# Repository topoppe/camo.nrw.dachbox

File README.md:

Im Rahmen des EFRE-geförderten Projektes CAMO.NRW forschen Mitarbeiter der Hochschule Ruhr West zusammen mit Kollegen der Bergischen Universität Wuppertal und der Bergischen Struktur- & Wirtschaftsförderungsgesellschaft an der Zukunft der automatisierten Mobilität. An der Hochschule bestand schon eine Experimentalplattform bestehend aus verschiedenen Kameras, Radarsensoren, LiDAR und mehreren GNSS.
Jene Plattform war im Kofferraum eines PKWs verbaut, jedoch ohne die Beachtung gängiger Sicherheitsvorschriften und Normen. 
Durch die komplexe Einbauweise war die gesamte Plattform an einen einzelnen PKW gebunden. 
Im Rahmen dieser Arbeit wurde die vorhandene Sensortechnik auf einem austauschbaren Geräteträger montiert. Hierbei wurde sowohl auf Sicherheitsvorschriften als auch auf die einfache Montagemöglichkeit auf verschiedenen PKW geachtet. 
Der entstandene Geräteträger kann nun sowohl mobil als auch stationär, auf einem beliebigen PKW montiert oder in einer Laborumgebung ohne PKW genutzt werden.

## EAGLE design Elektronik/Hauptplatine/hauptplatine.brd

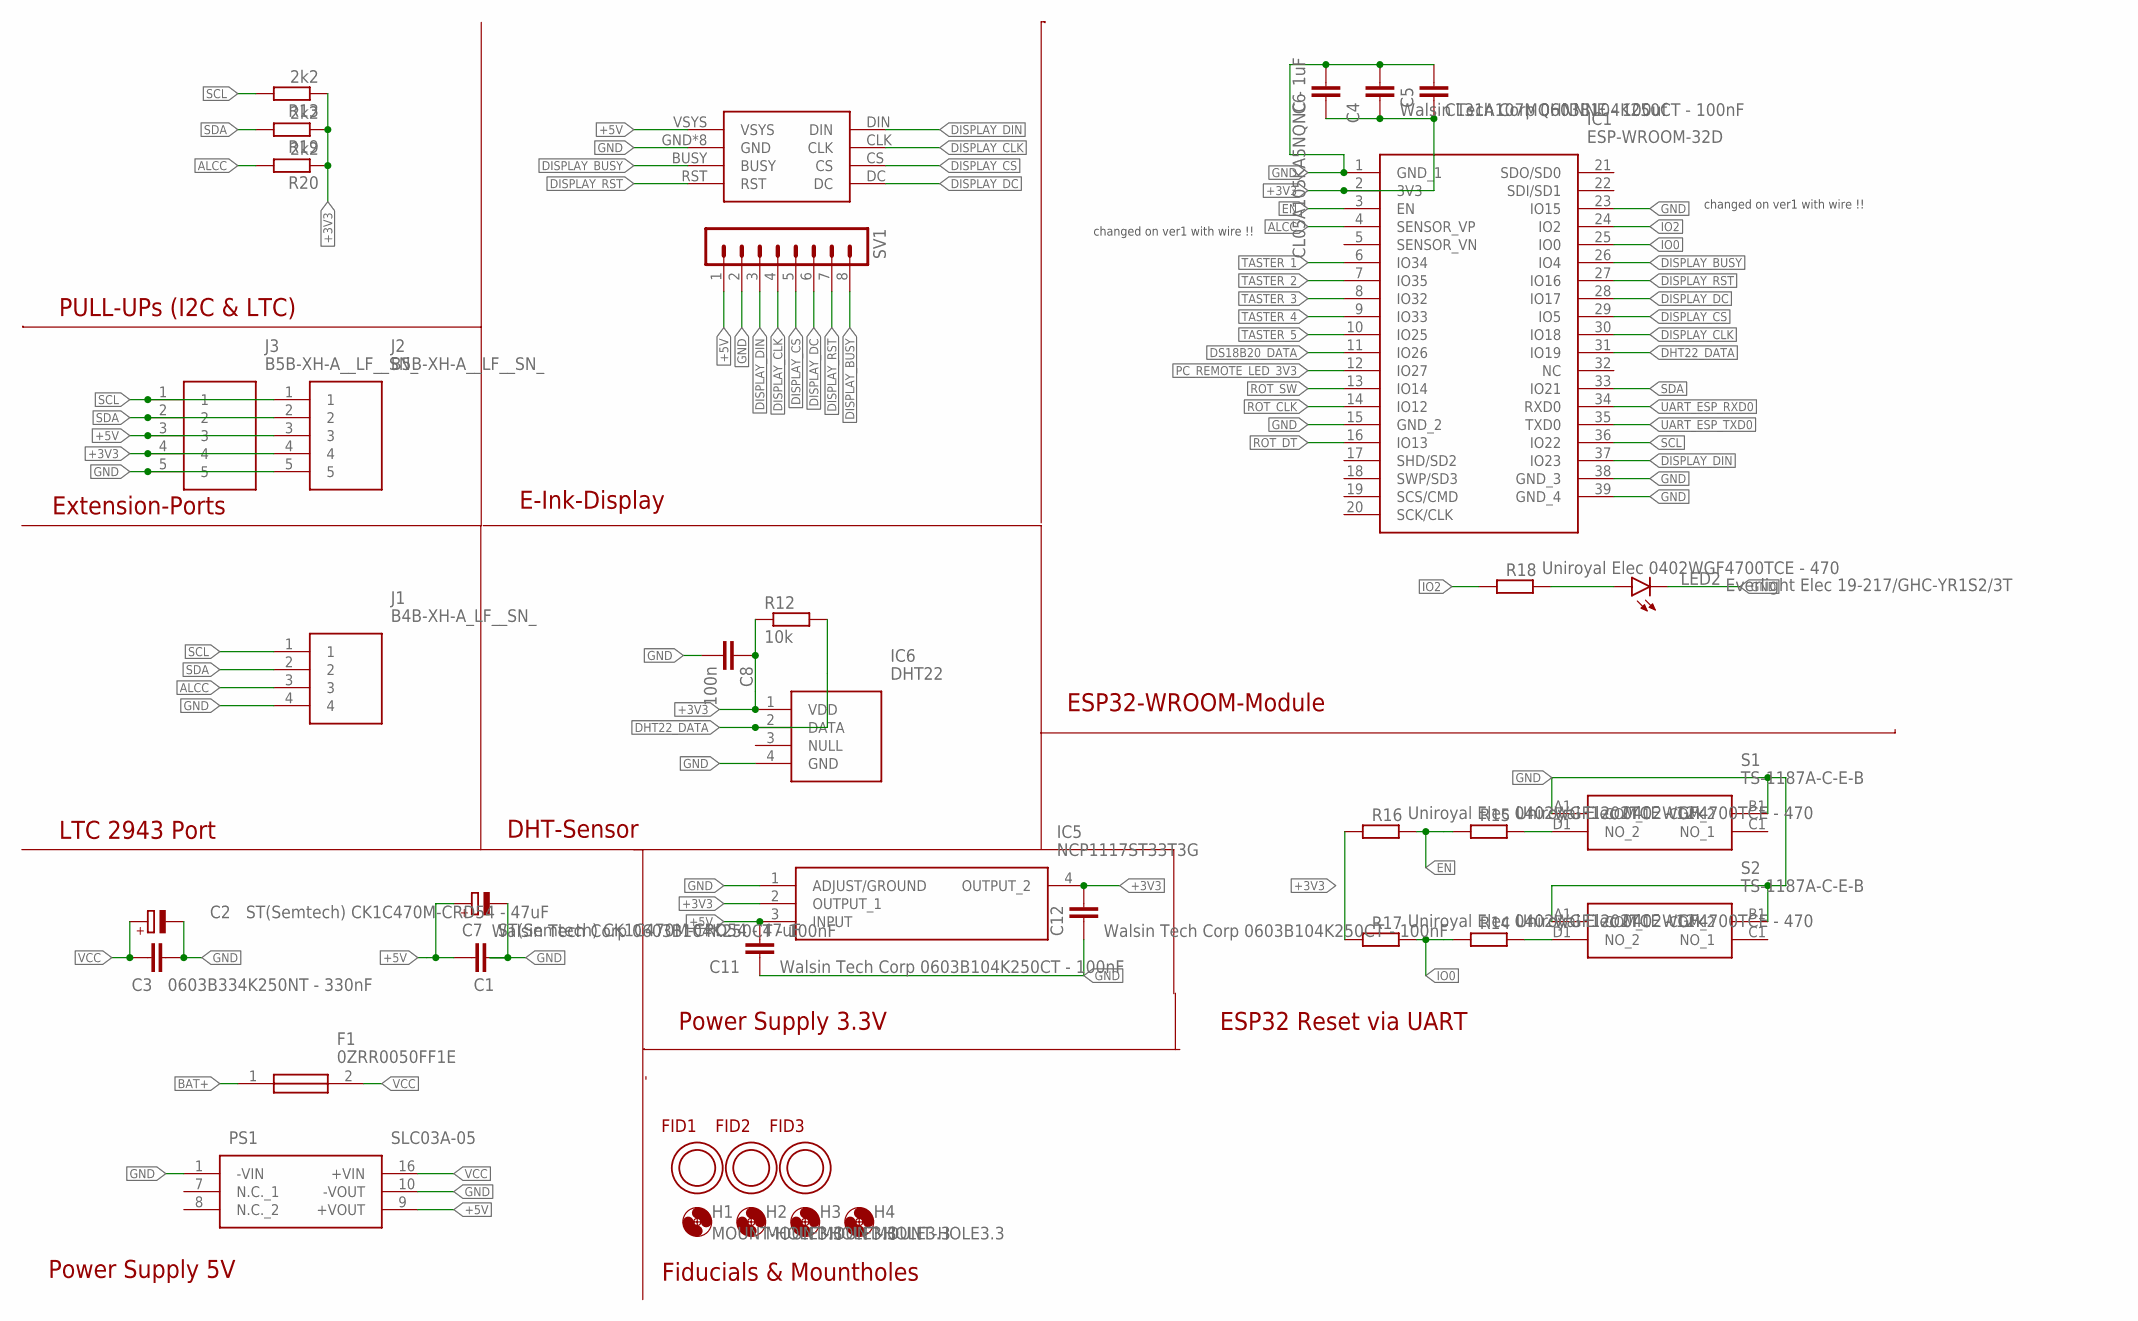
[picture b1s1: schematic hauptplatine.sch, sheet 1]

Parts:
C1, C4, C11, C12: Walsin Tech Corp 0603B104K250CT - 100nF; C0603
C2, C7: ST(Semtech) CK1C470M-CRD54 - 47uF; PANASONIC_C
C3: 0603B334K250NT - 330nF; C0603
C5: CL31A107MQHNNNE - 100uf; C1206
C6: CL05A105KA5NQNC - 1uF; C0402
C8: 100n; C1206
F1: 0ZRR0050FF1E
FID1, FID2, FID3: OPEN-PNP-FIDUCIAL
H1, H2, H3, H4: MOUNT-HOLE3.3; 3,3
IC1: ESP-WROOM-32D; ESPWROOM32D
IC5: NCP1117ST33T3G; SOT230P700X180-4N
IC6: DHT22
J1: B4B-XH-A_LF__SN_; B4BXHALFSN
J2, J3: B5B-XH-A__LF__SN_; SHDR5W64P0X250_1X5_1490X575X70
LED2: Everlight Elec 19-217/GHC-YR1S2/3T; CHIPLED_0603
PS1: SLC03A-05; SLC03A05
R12: 10k; R1206
R13, R19, R20: 2k2; R1206
R14, R15, R18: Uniroyal Elec 0402WGF4700TCE - 470; R0402
R16, R17: Uniroyal Elec 0402WGF1202TCE - 12k; R0402
S1, S2: TS-1187A-C-E-B; TS1187ACEB
SV1: MA08-1
U$1: PICO-EPAPER-2.9-V3

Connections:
+3V3: C4.1, C5.2, C6.1, C8.1, C12.2, IC1.2 (3V3), IC5.2 (OUTPUT_1), IC5.4 (OUTPUT_2), IC6.1 (VDD), J2.4, J3.4, R12.1, R13.1, R16.1, R17.1, R19.1, R20.1; also elsewhere on the board
+5V: C1.1, C7.+, C11.2, IC5.3 (INPUT), J2.3, J3.3, PS1.9 (+VOUT), SV1.1, U$1.VSYS; also elsewhere on the board
ALCC: IC1.4 (SENSOR_VP), J1.3, R20.2
BAT+: F1.1; also elsewhere on the board
DHT22_DATA: IC1.31 (IO19), IC6.2 (DATA), R12.2
DISPLAY_BUSY: IC1.26 (IO4), SV1.8, U$1.BUSY
DISPLAY_CLK: IC1.30 (IO18), SV1.4, U$1.CLK
DISPLAY_CS: IC1.29 (IO5), SV1.5, U$1.CS
DISPLAY_DC: IC1.28 (IO17), SV1.6, U$1.DC
DISPLAY_DIN: IC1.37 (IO23), SV1.3, U$1.DIN
DISPLAY_RST: IC1.27 (IO16), SV1.7, U$1.RST
DS18B20_DATA: IC1.11 (IO26); also elsewhere on the board
EN: IC1.3 (EN), R15.1, R16.2; also elsewhere on the board
GND: C1.2, C2.-, C3.1, C4.2, C5.1, C6.2, C7.-, C8.2, C11.1, C12.1, IC1.1 (GND_1), IC1.15 (GND_2), IC1.23 (IO15), IC1.38 (GND_3), IC1.39 (GND_4), IC5.1 (ADJUST/GROUND), IC6.4 (GND), J1.4, J2.5, J3.5, LED2.C, PS1.1 (-VIN), PS1.10 (-VOUT), S1.A1 (COM_1), S1.B1 (COM_2), S2.A1 (COM_1), S2.B1 (COM_2), SV1.2, U$1.GND, U$1.GND1 (GND), U$1.GND2 (GND), U$1.GND3 (GND), U$1.GND4 (GND), U$1.GND5 (GND), U$1.GND6 (GND), U$1.GND7 (GND); also elsewhere on the board
IO0: IC1.25 (IO0), R14.1, R17.2; also elsewhere on the board
IO2: IC1.24 (IO2), R18.1
unnamed: R15.2, S1.D1 (NO_2)
unnamed: R14.2, S2.D1 (NO_2)
unnamed: LED2.A, R18.2
PC_REMOTE_LED_3V3: IC1.12 (IO27); also elsewhere on the board
ROT_CLK: IC1.14 (IO12); also elsewhere on the board
ROT_DT: IC1.16 (IO13); also elsewhere on the board
ROT_SW: IC1.13 (IO14); also elsewhere on the board
SCL: IC1.36 (IO22), J1.1, J2.1, J3.1, R13.2; also elsewhere on the board
SDA: IC1.33 (IO21), J1.2, J2.2, J3.2, R19.2; also elsewhere on the board
TASTER_1: IC1.6 (IO34); also elsewhere on the board
TASTER_2: IC1.7 (IO35); also elsewhere on the board
TASTER_3: IC1.8 (IO32); also elsewhere on the board
TASTER_4: IC1.9 (IO33); also elsewhere on the board
TASTER_5: IC1.10 (IO25); also elsewhere on the board
UART_ESP_RXD0: IC1.34 (RXD0); also elsewhere on the board
UART_ESP_TXD0: IC1.35 (TXD0); also elsewhere on the board
VCC: C2.+, C3.2, F1.2, PS1.16 (+VIN); also elsewhere on the board

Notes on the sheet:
Power Supply 5V
changed on ver1 with wire !!
DHT-Sensor
Extension-Ports
PULL-UPs (I2C & LTC)
E-Ink-Display
LTC 2943 Port
ESP32-WROOM-Module
ESP32 Reset via UART
Power Supply 3.3V
Fiducials & Mountholes

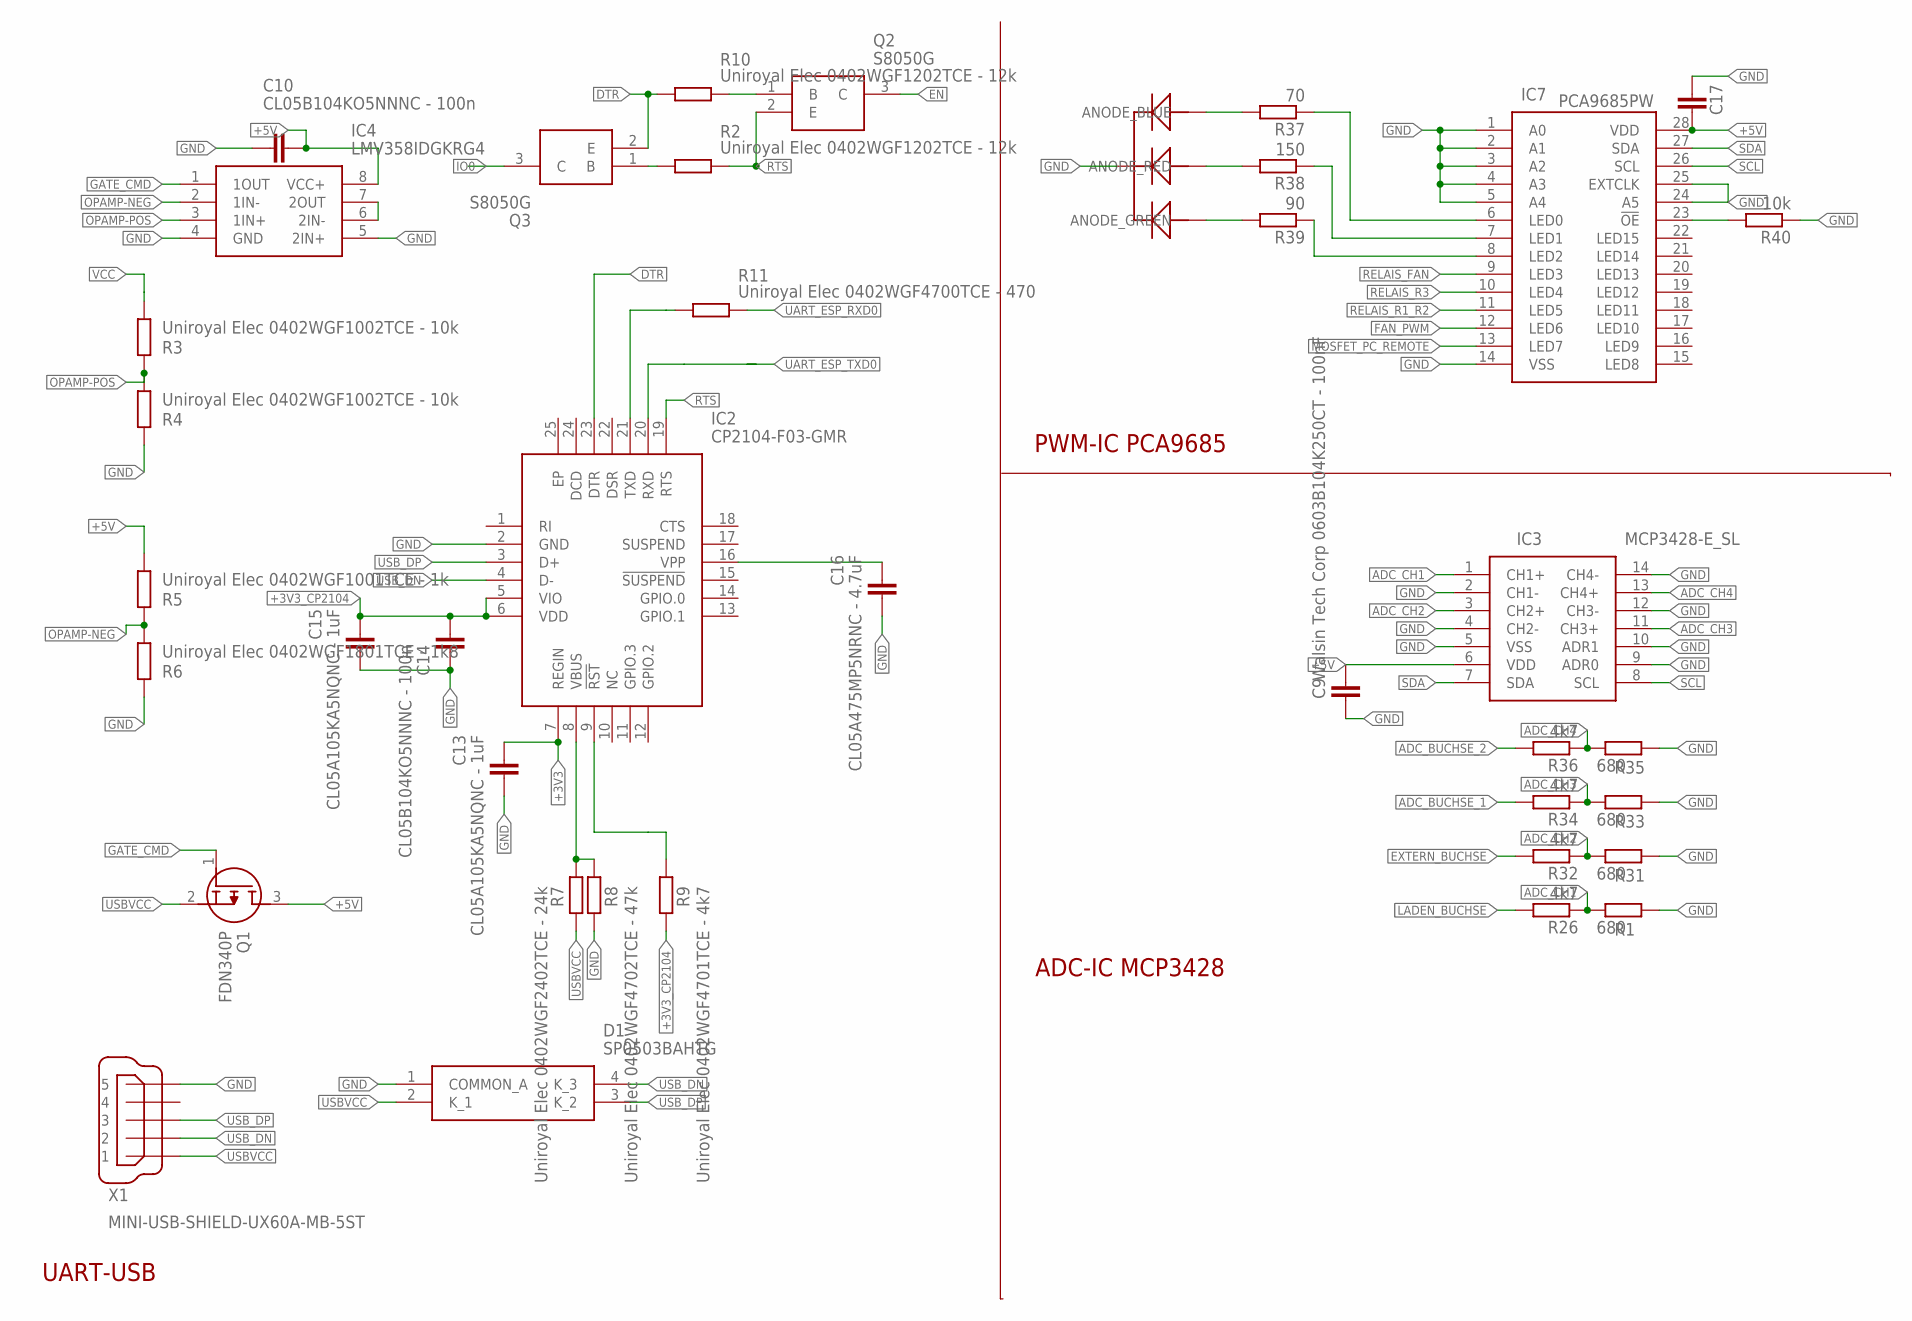
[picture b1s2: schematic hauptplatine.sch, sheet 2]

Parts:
C9, C17: Walsin Tech Corp 0603B104K250CT - 100nF; C0603
C10, C14: CL05B104KO5NNNC - 100n; C0402
C13, C15: CL05A105KA5NQNC - 1uF; C0402
C16: CL05A475MP5NRNC - 4.7uF; C0402
D1: SP0503BAHTG
IC2: CP2104-F03-GMR; QFN50P400X400X80-25N
IC3: MCP3428-E_SL; SOIC127P600X175-14N
IC4: LMV358IDGKRG4; SOP65P490X110-8N
IC7: PCA9685PW; SOP65P640X110-28N
Q1: FDN340P; SOT95P237X112-3N
Q2, Q3: S8050G; SOT95P240X110-3N
R1, R31, R33, R35: 680; R1206
R2, R10: Uniroyal Elec 0402WGF1202TCE - 12k; R0402
R3, R4: Uniroyal Elec 0402WGF1002TCE - 10k; R0402
R5: Uniroyal Elec 0402WGF1001TCE - 1k; R0402
R6: Uniroyal Elec 0402WGF1801TCE - 1k8; R0402
R7: Uniroyal Elec 0402WGF2402TCE - 24k; R0402
R8: Uniroyal Elec 0402WGF4702TCE - 47k; R0402
R9: Uniroyal Elec 0402WGF4701TCE - 4k7; R0402
R11: Uniroyal Elec 0402WGF4700TCE - 470; R0402
R26, R32, R34, R36: 4k7; R1206
R37: 70; R1206
R38: 150; R1206
R39: 90; R1206
R40: 10k; R1206
U$12: RG_LED_5MM; RGB_LED_5MM
X1: MINI-USB-SHIELD-UX60A-MB-5ST; UX60A-MB-5ST

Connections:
+3V3: C13.2, IC2.7 (REGIN); also elsewhere on the board
+3V3_CP2104: C14.2, C15.2, IC2.5 (VIO), IC2.6 (VDD), R9.2
+5V: C9.2, C10.2, C17.1, IC3.6 (VDD), IC4.8 (VCC+), IC7.28 (VDD), Q1.3 (D), R5.1; also elsewhere on the board
ADC_BUCHSE_1: R34.2; also elsewhere on the board
ADC_BUCHSE_2: R36.2; also elsewhere on the board
ADC_CH1: IC3.1 (CH1+), R1.1, R26.1
ADC_CH2: IC3.3 (CH2+), R31.1, R32.1
ADC_CH3: IC3.11 (CH3+), R33.1, R34.1
ADC_CH4: IC3.13 (CH4+), R35.1, R36.1
DTR: IC2.23 (DTR), Q3.2 (E), R10.1
EN: Q2.3 (C); also elsewhere on the board
EXTERN_BUCHSE: R32.2; also elsewhere on the board
FAN_PWM: IC7.12 (LED6); also elsewhere on the board
GATE_CMD: IC4.1 (1OUT), Q1.1 (G)
GND: C9.1, C10.1, C13.1, C14.1, C15.1, C16.1, C17.2, D1.1 (COMMON_A), IC2.2 (GND), IC3.2 (CH1-), IC3.4 (CH2-), IC3.5 (VSS), IC3.9 (ADR0), IC3.10 (ADR1), IC3.12 (CH3-), IC3.14 (CH4-), IC4.4 (GND), IC4.5 (2IN+), IC7.1 (A0), IC7.2 (A1), IC7.3 (A2), IC7.4 (A3), IC7.5 (A4), IC7.14 (VSS), IC7.24 (A5), IC7.25 (EXTCLK), R1.2, R4.2, R6.2, R8.2, R31.2, R33.2, R35.2, R40.1, U$12.CATHODE, X1.5; also elsewhere on the board
IO0: Q3.3 (C); also elsewhere on the board
LADEN_BUCHSE: R26.2; also elsewhere on the board
MOSFET_PC_REMOTE: IC7.13 (LED7); also elsewhere on the board
unnamed: Q3.1 (B), R2.1
unnamed: IC4.6 (2IN-), IC4.7 (2OUT)
unnamed: IC2.8 (VBUS), R7.1, R8.1
unnamed: IC2.9 (!RST), R9.1
unnamed: C16.2, IC2.16 (VPP)
unnamed: IC2.21 (TXD), R11.1
unnamed: Q2.1 (B), R10.2
unnamed: R39.2, U$12.ANODE_GREEN
unnamed: R37.2, U$12.ANODE_BLUE
unnamed: R38.2, U$12.ANODE_RED
unnamed: IC7.23 (!OE), R40.2
OPAMP-NEG: IC4.2 (1IN-), R5.2, R6.1
OPAMP-POS: IC4.3 (1IN+), R3.2, R4.1
RELAIS_FAN: IC7.9 (LED3); also elsewhere on the board
RELAIS_R1_R2: IC7.11 (LED5); also elsewhere on the board
RELAIS_R3: IC7.10 (LED4); also elsewhere on the board
RGB_BLAU1: IC7.6 (LED0), R37.1
RGB_GREEN1: IC7.8 (LED2), R39.1
RGB_ROT1: IC7.7 (LED1), R38.1
RTS: IC2.19 (RTS), Q2.2 (E), R2.2
SCL: IC3.8 (SCL), IC7.26 (SCL); also elsewhere on the board
SDA: IC3.7 (SDA), IC7.27 (SDA); also elsewhere on the board
UART_ESP_RXD0: R11.2; also elsewhere on the board
UART_ESP_TXD0: IC2.20 (RXD); also elsewhere on the board
USBVCC: D1.2 (K_1), Q1.2 (S), R7.2, X1.1
USB_DN: D1.4 (K_3), IC2.4 (D-), X1.2
USB_DP: D1.3 (K_2), IC2.3 (D+), X1.3
VCC: R3.1; also elsewhere on the board

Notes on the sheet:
UART-USB
PWM-IC PCA9685
ADC-IC MCP3428

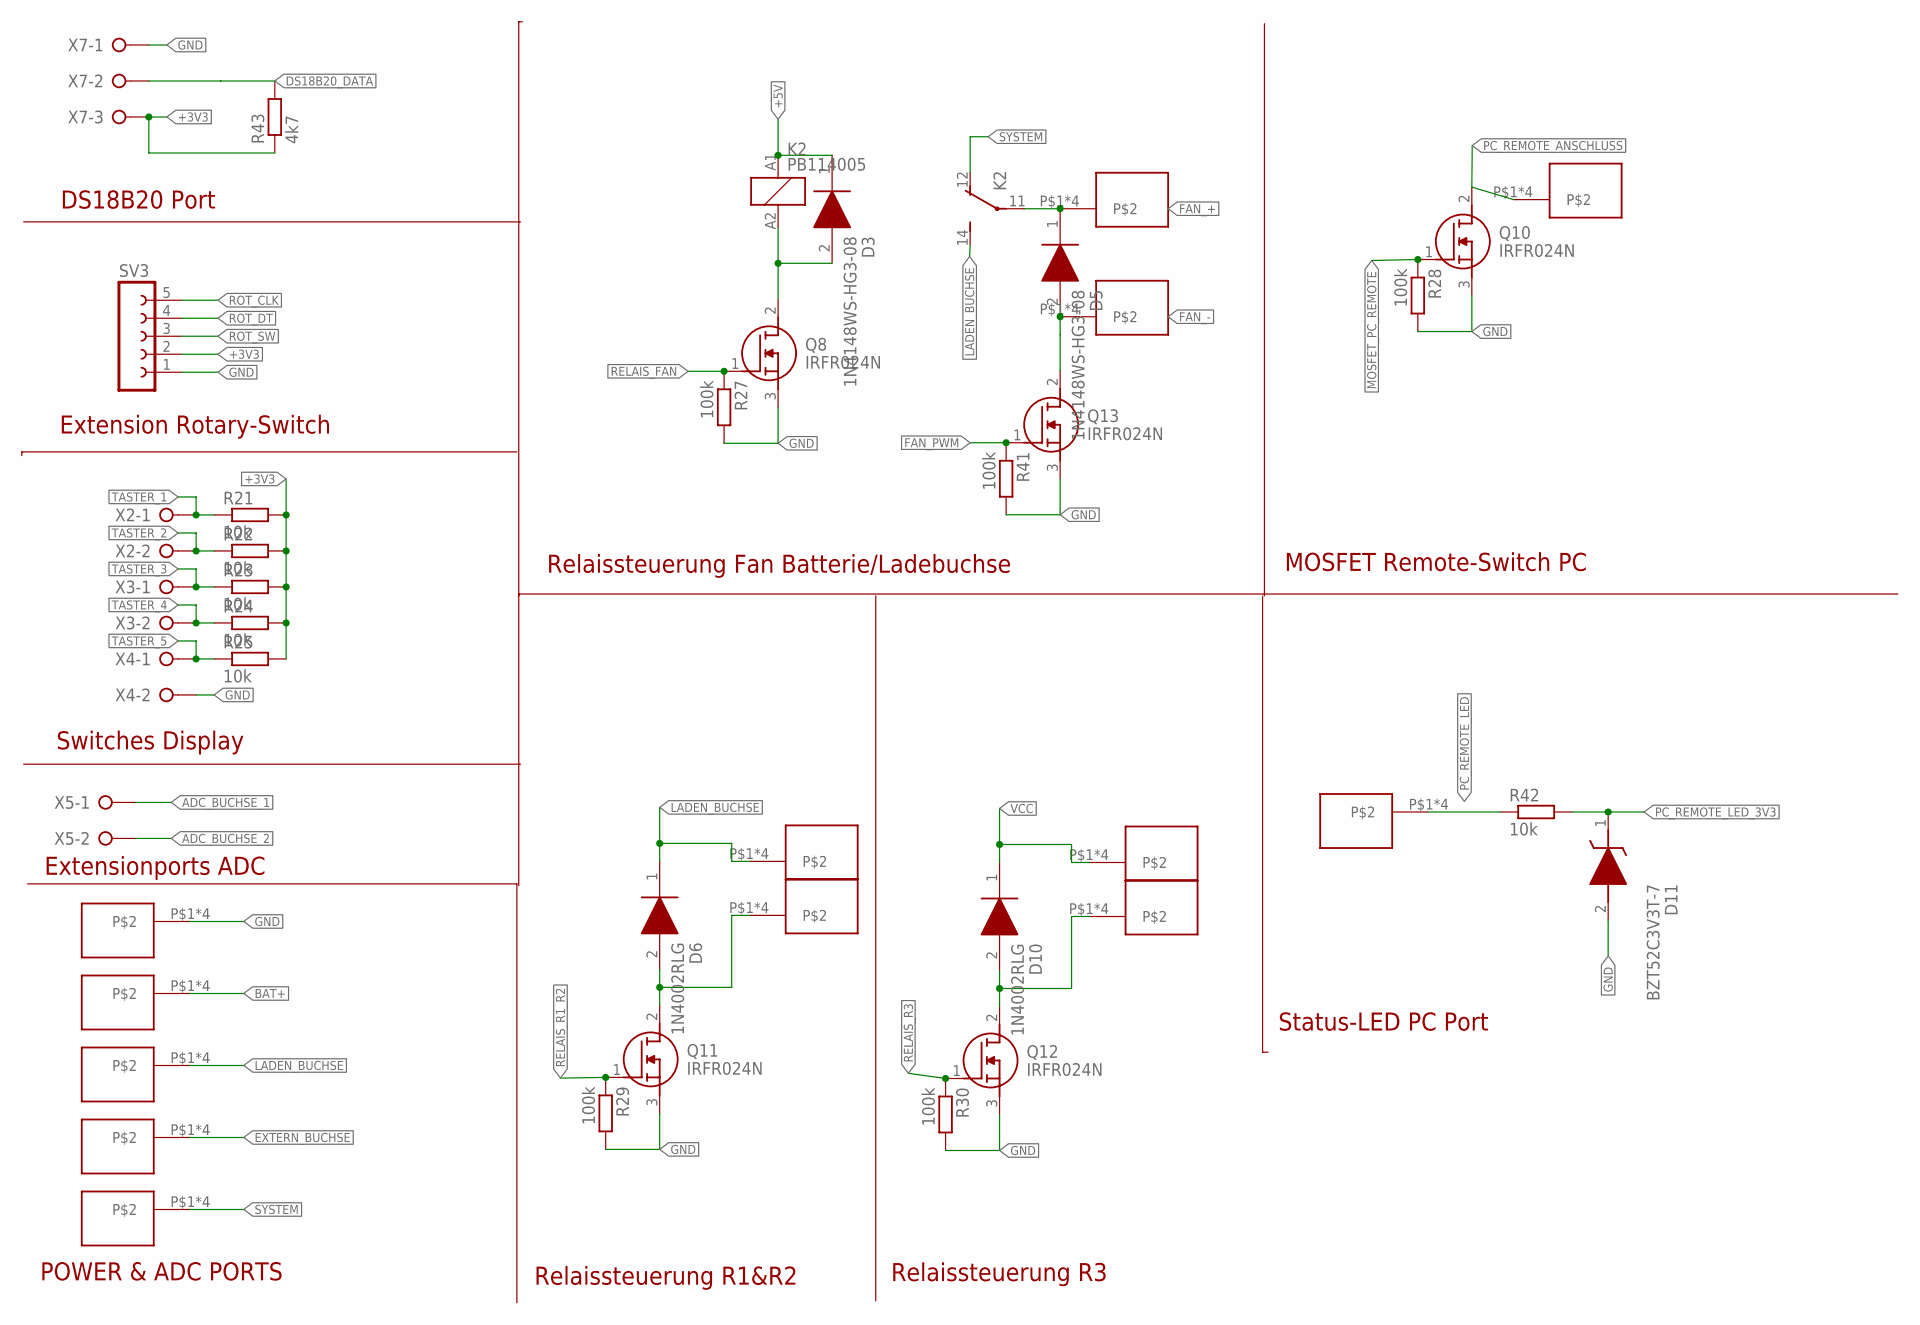
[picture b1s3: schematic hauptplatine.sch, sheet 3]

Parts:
D3, D5: 1N4148WS-HG3-08; SOD2713X115N
D6, D10: 1N4002RLG; DIOAD1405W86L465D235
D11: BZT52C3V3T-7; SODFL1608X65N
K2: PB114005; PB
Q8, Q10, Q11, Q12, Q13: IRFR024N; IRFR024TRPBFBE3
R21, R22, R23, R24, R25: 10k; R0805
R27, R28, R29, R30, R41: 100k; R1206
R42: 10k; R1206
R43: 4k7; R0805
SV3: FE05-1
U$2, U$17, U$18, U$19, U$20, U$21, U$22, U$23, U$24, U$25, U$26, U$27, U$28: WE-REDCUBE-74650173
X2, X3, X4, X5: W237-02P; W237-132
X7: W237-3E

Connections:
+3V3: R21.2, R22.2, R23.2, R24.2, R25.2, R43.1, SV3.2, X7.3; also elsewhere on the board
+5V: D3.1 (K), K2.A1 (1); also elsewhere on the board
ADC_BUCHSE_1: X5.1; also elsewhere on the board
ADC_BUCHSE_2: X5.2; also elsewhere on the board
BAT+: U$17.P$1, U$17.P$2, U$17.P$3, U$17.P$4; also elsewhere on the board
DS18B20_DATA: R43.2, X7.2; also elsewhere on the board
EXTERN_BUCHSE: U$19.P$1, U$19.P$2, U$19.P$3, U$19.P$4; also elsewhere on the board
FAN_+: D5.1 (K), K2.11, U$24.P$1, U$24.P$2, U$24.P$3, U$24.P$4
FAN_-: D5.2 (A), Q13.2 (D), U$27.P$1, U$27.P$2, U$27.P$3, U$27.P$4
FAN_PWM: Q13.1 (G), R41.1; also elsewhere on the board
GND: D11.2 (A), Q8.3 (S), Q10.3 (S), Q11.3 (S), Q12.3 (S), Q13.3 (S), R27.2, R28.2, R29.2, R30.2, R41.2, SV3.1, U$2.P$1, U$2.P$2, U$2.P$3, U$2.P$4, X4.2, X7.1; also elsewhere on the board
LADEN_BUCHSE: D6.1 (K), K2.14 (S), U$18.P$1, U$18.P$2, U$18.P$3, U$18.P$4, U$21.P$1, U$21.P$2, U$21.P$3, U$21.P$4; also elsewhere on the board
MOSFET_PC_REMOTE: Q10.1 (G), R28.1; also elsewhere on the board
unnamed: D3.2 (A), K2.A2 (2), Q8.2 (D)
PC_REMOTE_ANSCHLUSS: Q10.2 (D), U$25.P$1, U$25.P$2, U$25.P$3, U$25.P$4
PC_REMOTE_LED: R42.1, U$28.P$1, U$28.P$2, U$28.P$3, U$28.P$4
PC_REMOTE_LED_3V3: D11.1 (K), R42.2; also elsewhere on the board
RELAIS_FAN: Q8.1 (G), R27.1; also elsewhere on the board
RELAIS_R1_R2: Q11.1 (G), R29.1; also elsewhere on the board
RELAIS_R1_R2_ANSCHLUSS: D6.2 (A), Q11.2 (D), U$20.P$1, U$20.P$2, U$20.P$3, U$20.P$4
RELAIS_R3: Q12.1 (G), R30.1; also elsewhere on the board
RELAIS_R3_ANSCHLUSS: D10.2 (A), Q12.2 (D), U$22.P$1, U$22.P$2, U$22.P$3, U$22.P$4
ROT_CLK: SV3.5; also elsewhere on the board
ROT_DT: SV3.4; also elsewhere on the board
ROT_SW: SV3.3; also elsewhere on the board
SYSTEM: K2.12 (O), U$26.P$1, U$26.P$2, U$26.P$3, U$26.P$4
TASTER_1: R21.1, X2.1; also elsewhere on the board
TASTER_2: R22.1, X2.2; also elsewhere on the board
TASTER_3: R23.1, X3.1; also elsewhere on the board
TASTER_4: R24.1, X3.2; also elsewhere on the board
TASTER_5: R25.1, X4.1; also elsewhere on the board
VCC: D10.1 (K), U$23.P$1, U$23.P$2, U$23.P$3, U$23.P$4; also elsewhere on the board

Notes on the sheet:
POWER & ADC PORTS
Extensionports ADC
Switches Display
Extension Rotary-Switch
DS18B20 Port
Relaissteuerung R1&R2
Relaissteuerung R3
Relaissteuerung Fan Batterie/Ladebuchse
MOSFET Remote-Switch PC
Status-LED PC Port

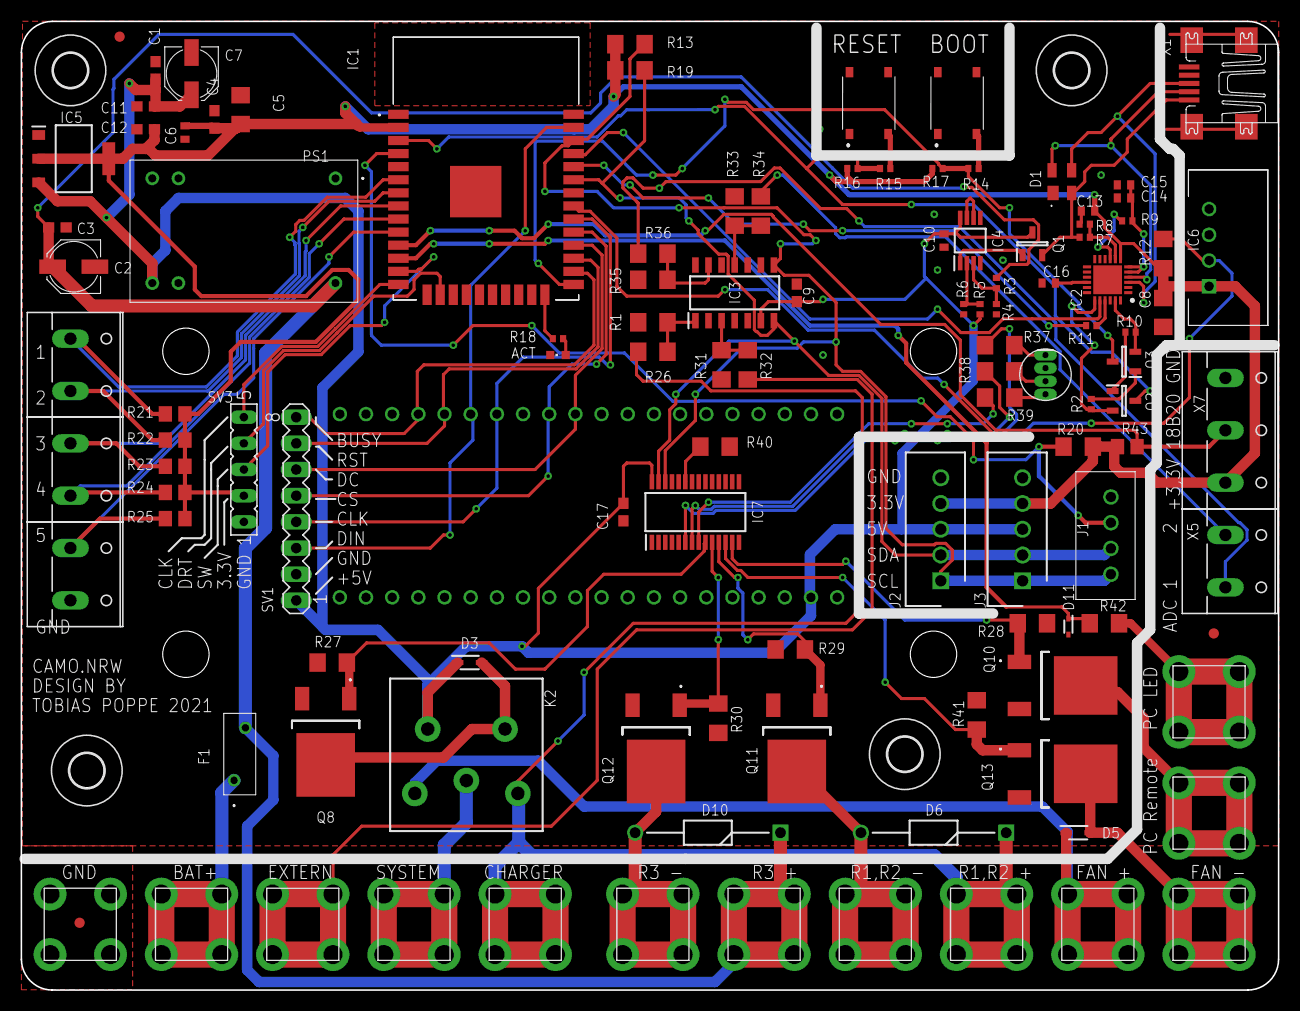
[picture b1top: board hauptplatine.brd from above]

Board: 2 copper layers, 122.0 x 94.0 mm, 120 parts (1 on the bottom side), 77 nets.

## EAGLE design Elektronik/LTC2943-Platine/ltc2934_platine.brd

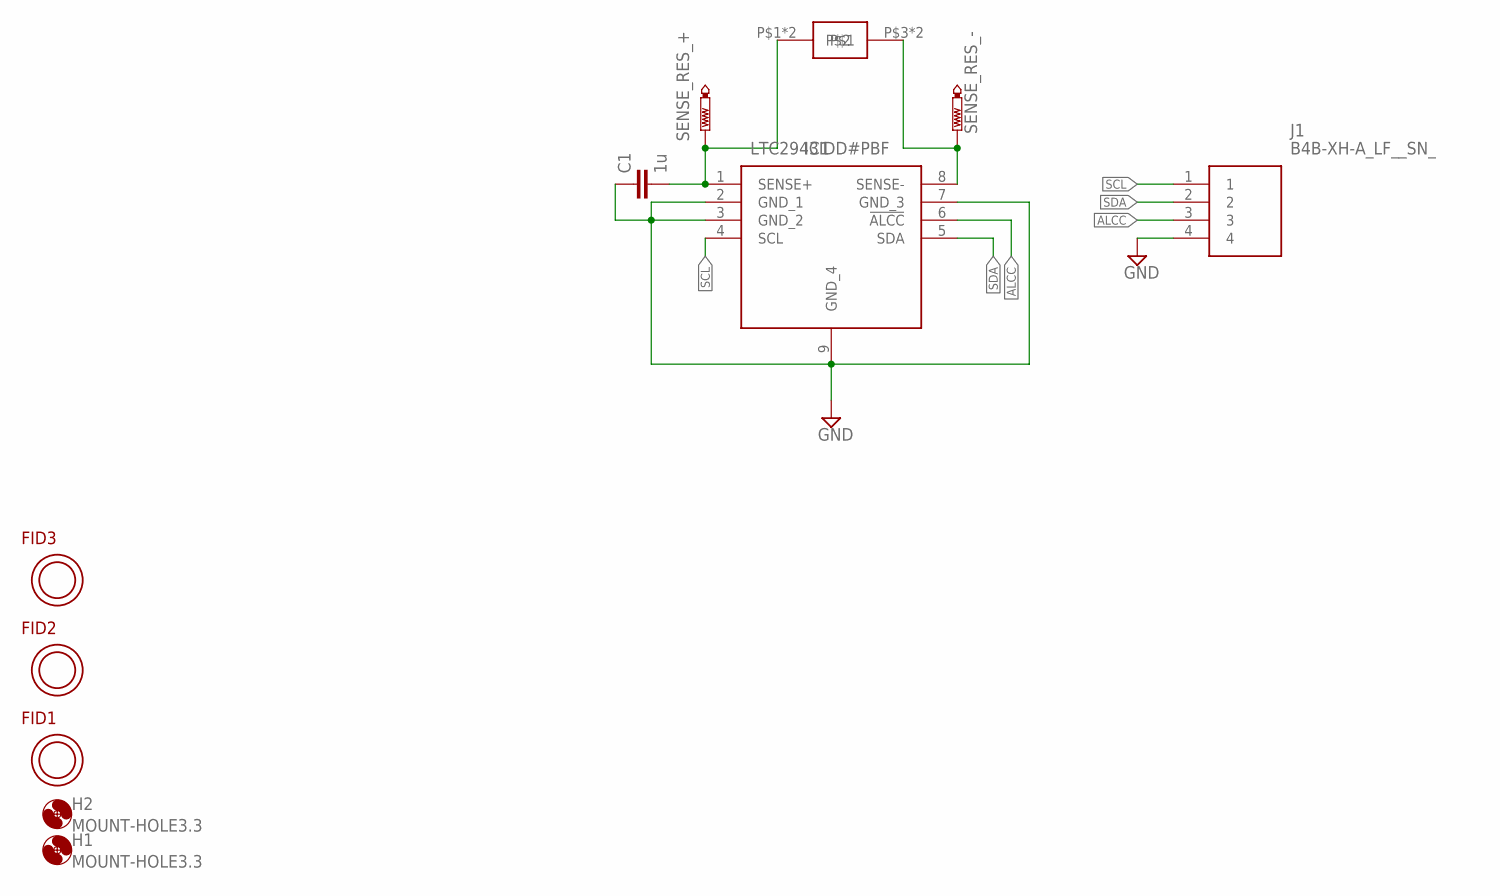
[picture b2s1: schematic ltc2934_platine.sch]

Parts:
C1: 1u; C1206
FID1, FID2, FID3: OPEN-PNP-FIDUCIAL
H1, H2: MOUNT-HOLE3.3; 3,3
IC1: LTC2943IDD#PBF; SON50P300X300X80-9N
J1: B4B-XH-A_LF__SN_; B4BXHALFSN
SENSE_RES_+: PTR1PAD1-13Y; P1-13Y
SENSE_RES_-: PTR1PAD1-13Y; P1-13Y
U$1: SHUNT_50A_75MV

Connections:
ALCC: IC1.6 (!ALCC), J1.3
GND: C1.1, IC1.2 (GND_1), IC1.3 (GND_2), IC1.7 (GND_3), IC1.9 (GND_4), J1.4
SCL: IC1.4 (SCL), J1.1
SDA: IC1.5 (SDA), J1.2
SENSE+: C1.2, IC1.1 (SENSE+), SENSE_RES_+.TP, U$1.P$1, U$1.P$6
SENSE_-: IC1.8 (SENSE-), SENSE_RES_-.TP, U$1.P$3, U$1.P$5

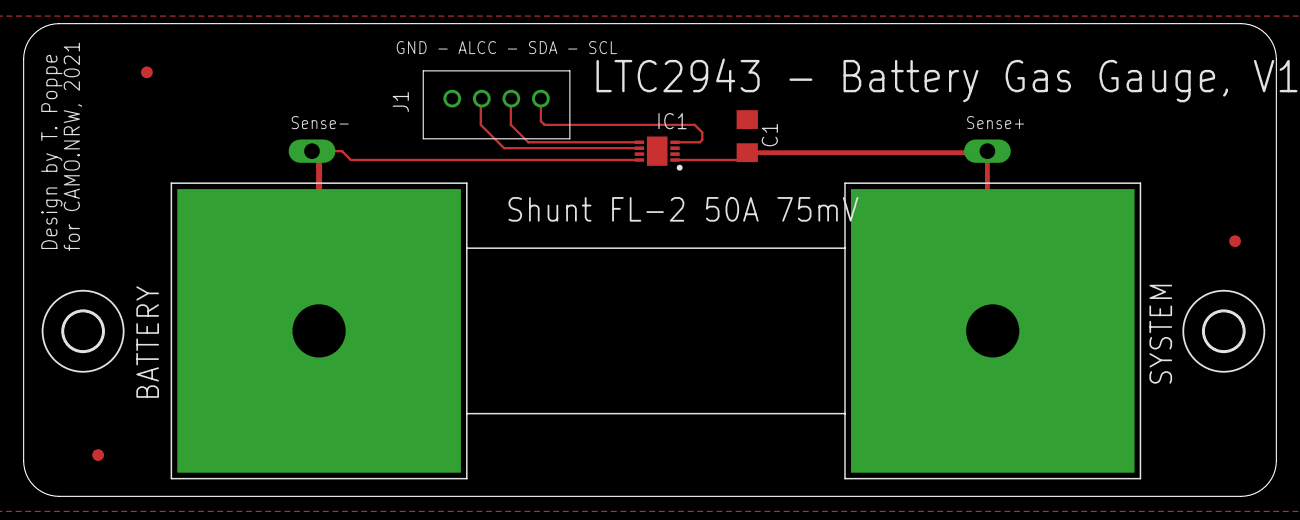
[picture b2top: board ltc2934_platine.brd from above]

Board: 2 copper layers, 106.0 x 40.0 mm, 11 parts (0 on the bottom side), 6 nets.

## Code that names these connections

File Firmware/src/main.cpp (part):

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#define DHTPIN 19
#define DS18B20_PIN 26
#define LTC2943_ALCC_PIN 36
#define taster_1_PIN 34
#define taster_2_PIN 35
#define taster_3_PIN 32
#define taster_4_PIN 33
#define taster_5_PIN 25
#define pc_remote_led_PIN 27
#define on_board_led_PIN 2

#define pwm_port_rgb_led_blau 0
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void gpio_setup()
{
  pinMode(LTC2943_ALCC_PIN, INPUT);
  pinMode(taster_1_PIN, INPUT);
  pinMode(taster_2_PIN, INPUT);
  pinMode(taster_3_PIN, INPUT);
  pinMode(taster_4_PIN, INPUT);
  pinMode(taster_5_PIN, INPUT);
  pinMode(pc_remote_led_PIN, INPUT);
  pinMode(on_board_led_PIN, OUTPUT);
}

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
      while (refresh_display_busy_flag == true)
      {
        if (!digitalRead(taster_1_PIN))
          pc_remote_mosfet(true);
        else
          pc_remote_mosfet(false);
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    esp_was_in_deepsleep = false;
    relais_mode = 0;
    data_to_show.system_status = 1;
    if (!digitalRead(taster_1_PIN))
      pc_remote_mosfet(true);
    else
      pc_remote_mosfet(false);

    if (digitalRead(pc_remote_led_PIN))
      set_rgb_led(255, 0, 0);
    else
      set_rgb_led(0, 0, 0);

    if (digitalRead(pc_remote_led_PIN))
      switch_sys_off_at_time = millis() + 30000;

    if (millis() > switch_sys_off_at_time)
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      relais_switch_system_on_bat(true);
      while (refresh_display_busy_flag == true)
      {
        if (!digitalRead(taster_1_PIN))
          pc_remote_mosfet(true);
        else
          pc_remote_mosfet(false);
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
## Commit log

2021-10-28 Commit readme
2021-10-28 Elektronik und Firmware
2021-10-29 Doku und Mechanik hochgeladen
